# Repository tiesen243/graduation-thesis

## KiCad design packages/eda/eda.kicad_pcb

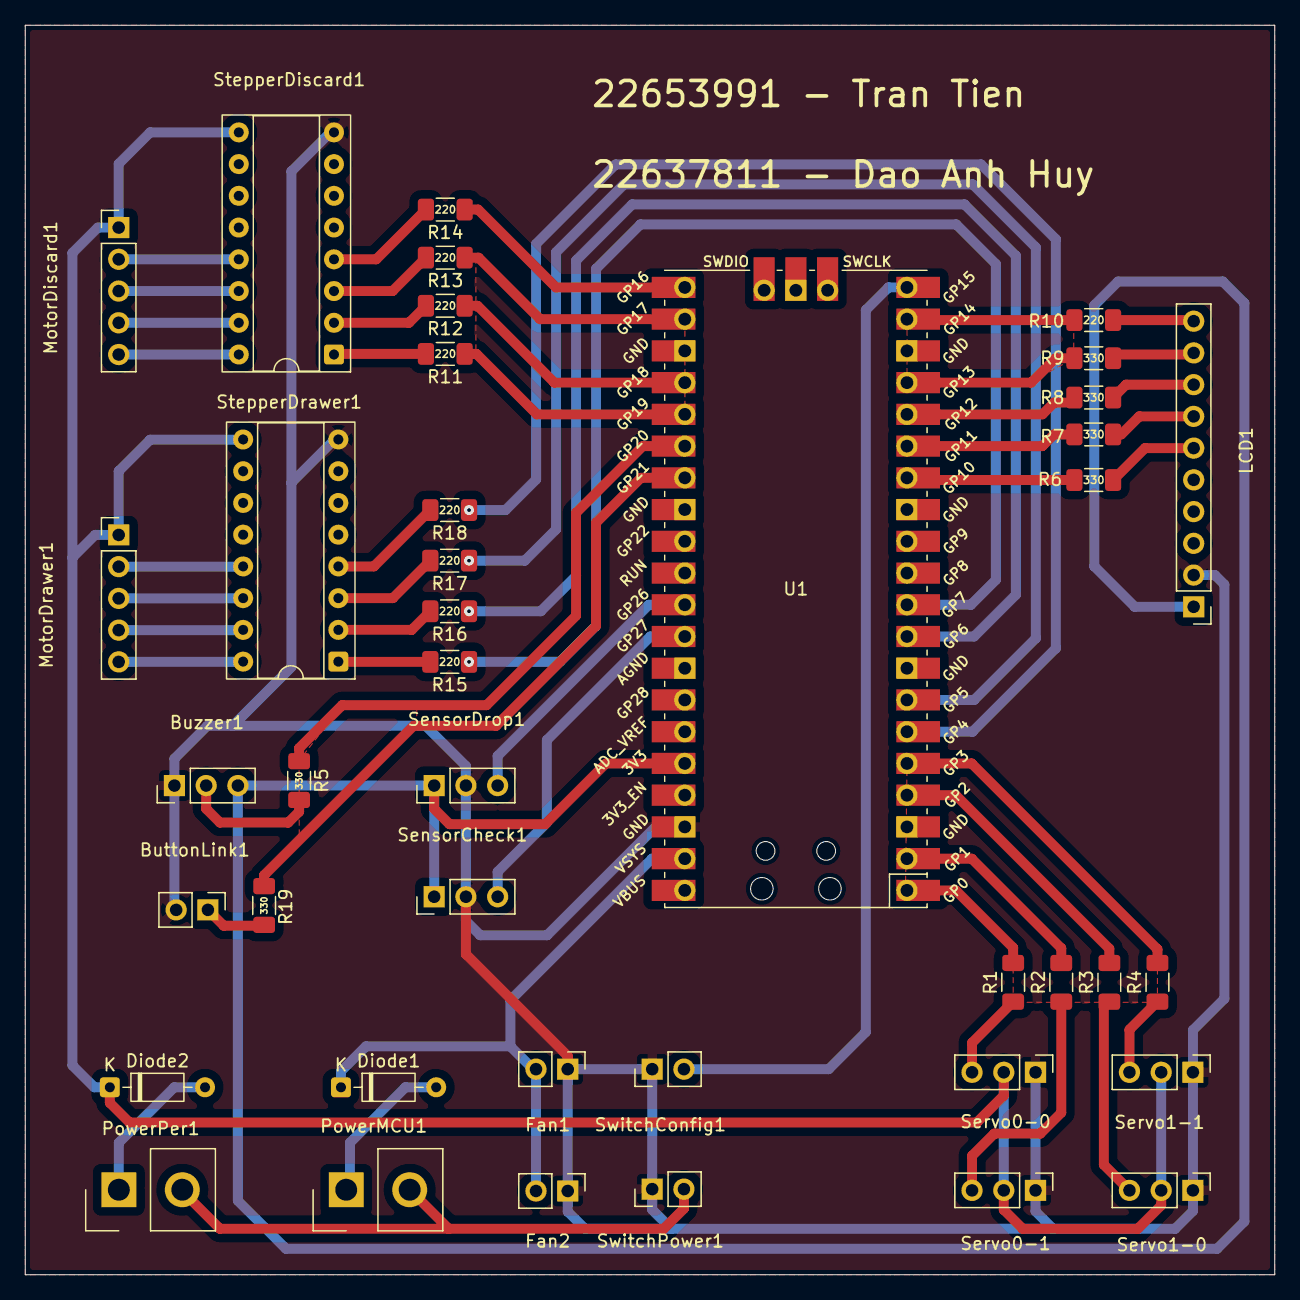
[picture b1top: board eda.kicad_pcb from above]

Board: 2 copper layers, 100.0 x 100.0 mm, 41 parts (0 on the bottom side), 56 nets.

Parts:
ButtonLink1: PinHeader_1x02_P2.54mm_Vertical
Buzzer1: PinHeader_1x03_P2.54mm_Vertical
Diode1, Diode2: D_DO-35_SOD27_P7.62mm_Horizontal
Fan1, Fan2: PinHeader_1x02_P2.54mm_Vertical
LCD1: PinHeader_1x10_P2.54mm_Vertical
MotorDiscard1: PinHeader_1x05_P2.54mm_Vertical
MotorDrawer1: PinHeader_1x05_P2.54mm_Vertical
PowerMCU1: Samtec_HPM-02-01-x-S_Straight_1x02_Pitch5.08mm
PowerPer1: Samtec_HPM-02-01-x-S_Straight_1x02_Pitch5.08mm
R1, R2, R3, R4, R5, R6, R7, R8, R9, R19: 330; R_1206_3216Metric_Pad1.30x1.75mm_HandSolder
R10, R11, R12, R13, R14, R15, R16, R17, R18: 220; R_1206_3216Metric_Pad1.30x1.75mm_HandSolder
SensorCheck1: PinHeader_1x03_P2.54mm_Vertical
SensorDrop1: PinHeader_1x03_P2.54mm_Vertical
Servo0-0, Servo0-1, Servo1-0, Servo1-1: PinHeader_1x03_P2.54mm_Vertical
StepperDiscard1: DIP-16_W7.62mm_Socket
StepperDrawer1: DIP-16_W7.62mm_Socket
SwitchConfig1: PinHeader_1x02_P2.54mm_Vertical
SwitchPower1: PinHeader_1x02_P2.54mm_Vertical
U1: Pico; RPi_Pico_SMD_TH

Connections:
/3.3V: Buzzer1.3, LCD1.1, SensorCheck1.1, SensorDrop1.1, U1.36 (3V3)
/5V: Diode2.1 (K), MotorDiscard1.1, MotorDrawer1.1, Servo0-0.2, Servo0-1.2, Servo1-0.2, Servo1-1.2, StepperDiscard1.9 (COM), StepperDrawer1.9 (COM)
/BTN: R19.2, U1.27 (GPIO21)
/Buzzer: R5.2, U1.26 (GPIO20)
/GND: ButtonLink1.2, Buzzer1.1, Fan1.1, Fan2.1, LCD1.2, SensorCheck1.2, SensorDrop1.2, Servo0-0.1, Servo0-1.1, Servo1-0.1, Servo1-1.1, StepperDiscard1.8 (GND), StepperDrawer1.8 (GND), SwitchConfig1.1, SwitchPower1.1, U1.38 (GND)
/GNDP: PowerMCU1.2, PowerPer1.2, SwitchPower1.2
/LCD_CLK: R6.2, U1.14 (GPIO10)
/LCD_CS: R10.2, U1.19 (GPIO14)
/LCD_RS: R8.2, U1.16 (GPIO12)
/LCD_RST: R9.2, U1.17 (GPIO13)
/LCD_SDA: R7.2, U1.15 (GPIO11)
/SC: SensorCheck1.3, U1.32 (GPIO27_ADC1)
/SD: SensorDrop1.3, U1.31 (GPIO26_ADC0)
/SW: SwitchConfig1.2, U1.20 (GPIO15)
/Serv00: R1.2, U1.1 (GPIO0)
/Serv01: R2.2, U1.2 (GPIO1)
/Serv10: R3.2, U1.4 (GPIO2)
/Serv11: R4.2, U1.5 (GPIO3)
/StD11: R18.1, U1.6 (GPIO4)
/StD12: R17.1, U1.7 (GPIO5)
/StD13: R16.1, U1.9 (GPIO6)
/StD14: R15.1, U1.10 (GPIO7)
/StD21: R14.1, U1.21 (GPIO16)
/StD22: R13.1, U1.22 (GPIO17)
/StD23: R12.1, U1.24 (GPIO18)
/StD24: R11.1, U1.25 (GPIO19)
/VCC: Diode1.1 (K), Fan1.2, Fan2.2, U1.39 (VSYS)
unnamed: ButtonLink1.1, R19.1
unnamed: Buzzer1.2, R5.1
unnamed: Diode1.2 (A), PowerMCU1.1
unnamed: Diode2.2 (A), PowerPer1.1
unnamed: LCD1.6, R6.1
unnamed: LCD1.7, R7.1
unnamed: LCD1.8, R8.1
unnamed: LCD1.9, R9.1
unnamed: LCD1.10, R10.1
unnamed: MotorDiscard1.2, StepperDiscard1.13 (O4)
unnamed: MotorDiscard1.3, StepperDiscard1.14 (O3)
unnamed: MotorDiscard1.4, StepperDiscard1.15 (O2)
unnamed: MotorDiscard1.5, StepperDiscard1.16 (O1)
unnamed: MotorDrawer1.2, StepperDrawer1.13 (O4)
unnamed: MotorDrawer1.3, StepperDrawer1.14 (O3)
unnamed: MotorDrawer1.4, StepperDrawer1.15 (O2)
unnamed: MotorDrawer1.5, StepperDrawer1.16 (O1)
unnamed: R1.1, Servo0-0.3
unnamed: R2.1, Servo0-1.3
unnamed: R3.1, Servo1-0.3
unnamed: R4.1, Servo1-1.3
unnamed: R11.2, StepperDiscard1.1 (I1)
unnamed: R12.2, StepperDiscard1.2 (I2)
unnamed: R13.2, StepperDiscard1.3 (I3)
unnamed: R14.2, StepperDiscard1.4 (I4)
unnamed: R15.2, StepperDrawer1.1 (I1)
unnamed: R16.2, StepperDrawer1.2 (I2)
unnamed: R17.2, StepperDrawer1.3 (I3)
unnamed: R18.2, StepperDrawer1.4 (I4)
